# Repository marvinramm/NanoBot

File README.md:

# NanoBot

**Line-following robot for RoboCup Junior Rescue Line, where the PCB is the chassis. It has an ESP32, eight light sensors, two colour sensors, three ToF distance sensors, a gyro, a gripper arm, and its own firmware, NanoOS.**

I built the NanoBot in 2022–2023 as my RoboCup robot. The motors, wheels and sensors mount straight onto the PCB, so the robot needs no separate chassis and stays at 113 × 101 mm. I designed the electronics, the 3D-printed mechanics and the firmware myself, over two hardware revisions.

## The task

In Rescue Line, the robot follows a black line on its own through a course of tiles. Along the way it has to handle:

- gaps in the line
- intersections with green markers that set the direction
- speed bumps, ramps and obstacles

At the end, a silver strip marks the entrance to the evacuation zone.

## Features

- **PCB as chassis:** four DC motors in 3D-printed mounts, TPE tires that grip, and a TB6612FNG driver
- **Light sensor bar:**
  - phototransistors with white LEDs under a printed light shield
  - outer sensors on both sides
  - two TCS34725 colour sensors for the green markers
  - a reflection sensor for the silver strip
- **Three ToF distance sensors** (VL53L1X) for obstacles and walls
- **MPU6050 gyro** for ramps and exact turns
- **Two servo outputs**, e.g. for the gripper arm
- **0.96" OLED and rotary encoder** for:
  - a menu to start the run
  - calibration of light and colour values, stored in the EEPROM
  - sensor read-outs and a system check
- **Power:**
  - 2S Li-Po via XT30
  - USB-C charger with cell balancing
  - undervoltage protection and a battery switch
  - its own buck converter for constant motor speed
- **Over-the-air updates** over Wi-Fi, and a contest mode that starts the run right after power-on
- **Mount and 5 V / 4 A supply for an NVIDIA Jetson Nano** for image processing (REV1)

## How it works

```mermaid
flowchart LR
    PT["Phototransistors<br/>+ white LEDs"] --> MUX["CD74HC4067<br/>analog mux"] --> ESP["ESP32<br/>NanoOS"]
    TCA["TCA9548A I²C mux<br/>3 × VL53L1X · 2 × TCS34725"] <--> ESP
    BUS["I²C<br/>MPU6050 · OLED"] <--> ESP
    ENC["Rotary encoder"] --> ESP
    ESP --> SR["74HC595<br/>shift registers"]
    SR --> DRV["TB6612FNG"]
    ESP -- PWM --> DRV --> MOT["4 DC motors"]
    SR --> LED["Sensor LEDs<br/>RGB illumination"]
    ESP -- PWM --> SERVO["2 servos<br/>gripper arm"]
```

The ESP32 reads the phototransistors through the analog multiplexer. The colour and ToF sensors share one I²C address, so each one sits on its own channel of the TCA9548A. Shift registers save GPIOs: they set the motor directions and switch the sensor LEDs.

NanoOS keeps the line between the outer sensors with a proportional correction. It decides on every tile what to do (turn, green marker, gap, dead end, obstacle) and uses the gyro angle to switch to its own speeds on ramps and speed bumps.

## Revisions

| | REV1 (2022) | REV2 (2023) |
|---|---|---|
| **Status** | Stable, used with the Jetson Nano | Prototype with known issues (e.g. the reset button does not work) |
| **Light sensors** | 5 phototransistors, 2 × TCS34725 | 8 phototransistors incl. outer sensors and a reflection sensor, RGB illumination, 2 × TCS34725 |
| **Distance** | 3 × VL53L0X | 3 × VL53L1X |
| **Power** | LM2576 5 V / 4 A for the Jetson Nano, AMS1117 | adds USB-C charger, balancing, undervoltage protection, battery switch, motor buck converter |
| **Antenna** | 2 × U.FL | SMA |
| **Firmware** | [NanoOS 0.80](firmware/NanoOS-REV1) | [NanoOS 1.15](firmware/NanoOS) |

The lessons from both boards went into [**RoboCore**](https://github.com/marvinramm/RoboCore). RoboCore is a much smaller Raspberry Pi HAT that splits real-time control (ESP32-S3) and image processing (Pi).

## Repository layout

```
firmware/NanoOS/          NanoOS 1.15 for REV2 (Arduino sketch)
firmware/NanoOS-REV1/     NanoOS 0.80, the last version for REV1
hardware/nanobot-rev1/    Schematic, BOM, ESP32 pin assignment
hardware/nanobot-rev2/    Schematic, BOM, ESP32 pin assignment, EAGLE source
hardware/mechanical/      3D-printed parts: motor mounts, rims, tires, light shields, encoder knob
docs/images/              Pictures used in this README
```

Gerber files and ready-to-flash firmware images are attached to the [releases](https://github.com/marvinramm/NanoBot/releases). Libraries, Arduino settings and flashing are described in [`firmware/README.md`](firmware/README.md).

## License

© 2022–2023 Marvin Ramm. Open source with attribution:

- Code (`firmware/`): [MIT](LICENSE)
- Hardware and documentation: [CC BY 4.0](hardware/LICENSE)

Commercial use is allowed. Credit "NanoBot by Marvin Ramm" with a link to this repository. Details are in [LICENSING.md](LICENSING.md).

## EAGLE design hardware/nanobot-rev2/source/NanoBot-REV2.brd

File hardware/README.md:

# Hardware

| Folder | Content |
|---|---|
| [`nanobot-rev1`](nanobot-rev1) | REV1 (November 2022): schematic (PDF), BOM, ESP32 pin assignment |
| [`nanobot-rev2`](nanobot-rev2) | REV2 (April 2023): schematic (PDF), BOM with LCSC part numbers, ESP32 pin assignment, EAGLE 9.6 schematic and board in `source/` |
| [`mechanical`](mechanical) | 3D-printed parts (3MF / STL) |

The Gerber, drill and pick-and-place files of both revisions are attached to the [releases](https://github.com/marvinramm/NanoBot/releases).

**Build REV1.** REV2 works only partly (e.g. the reset button does not work) and is published as a reference for its power section: USB-C charger, cell balancing, undervoltage protection and battery switch.

The EAGLE source of REV2 uses parts from my own libraries; they are embedded in the `.sch` / `.brd` files, so the design opens without them.

## Pin assignment

The `*_ESP32_pinout.csv` files list every ESP32 GPIO with its function on the board. Sensors behind the analog multiplexer and the shift registers are mapped in `Pins.h` of the matching firmware ([REV2](../firmware/NanoOS/Pins.h), [REV1](../firmware/NanoOS-REV1/Pins.h)).

## License

The hardware design files, 3D models and documentation are licensed under [CC BY 4.0](LICENSE). See [LICENSING.md](../LICENSING.md) for the attribution text.

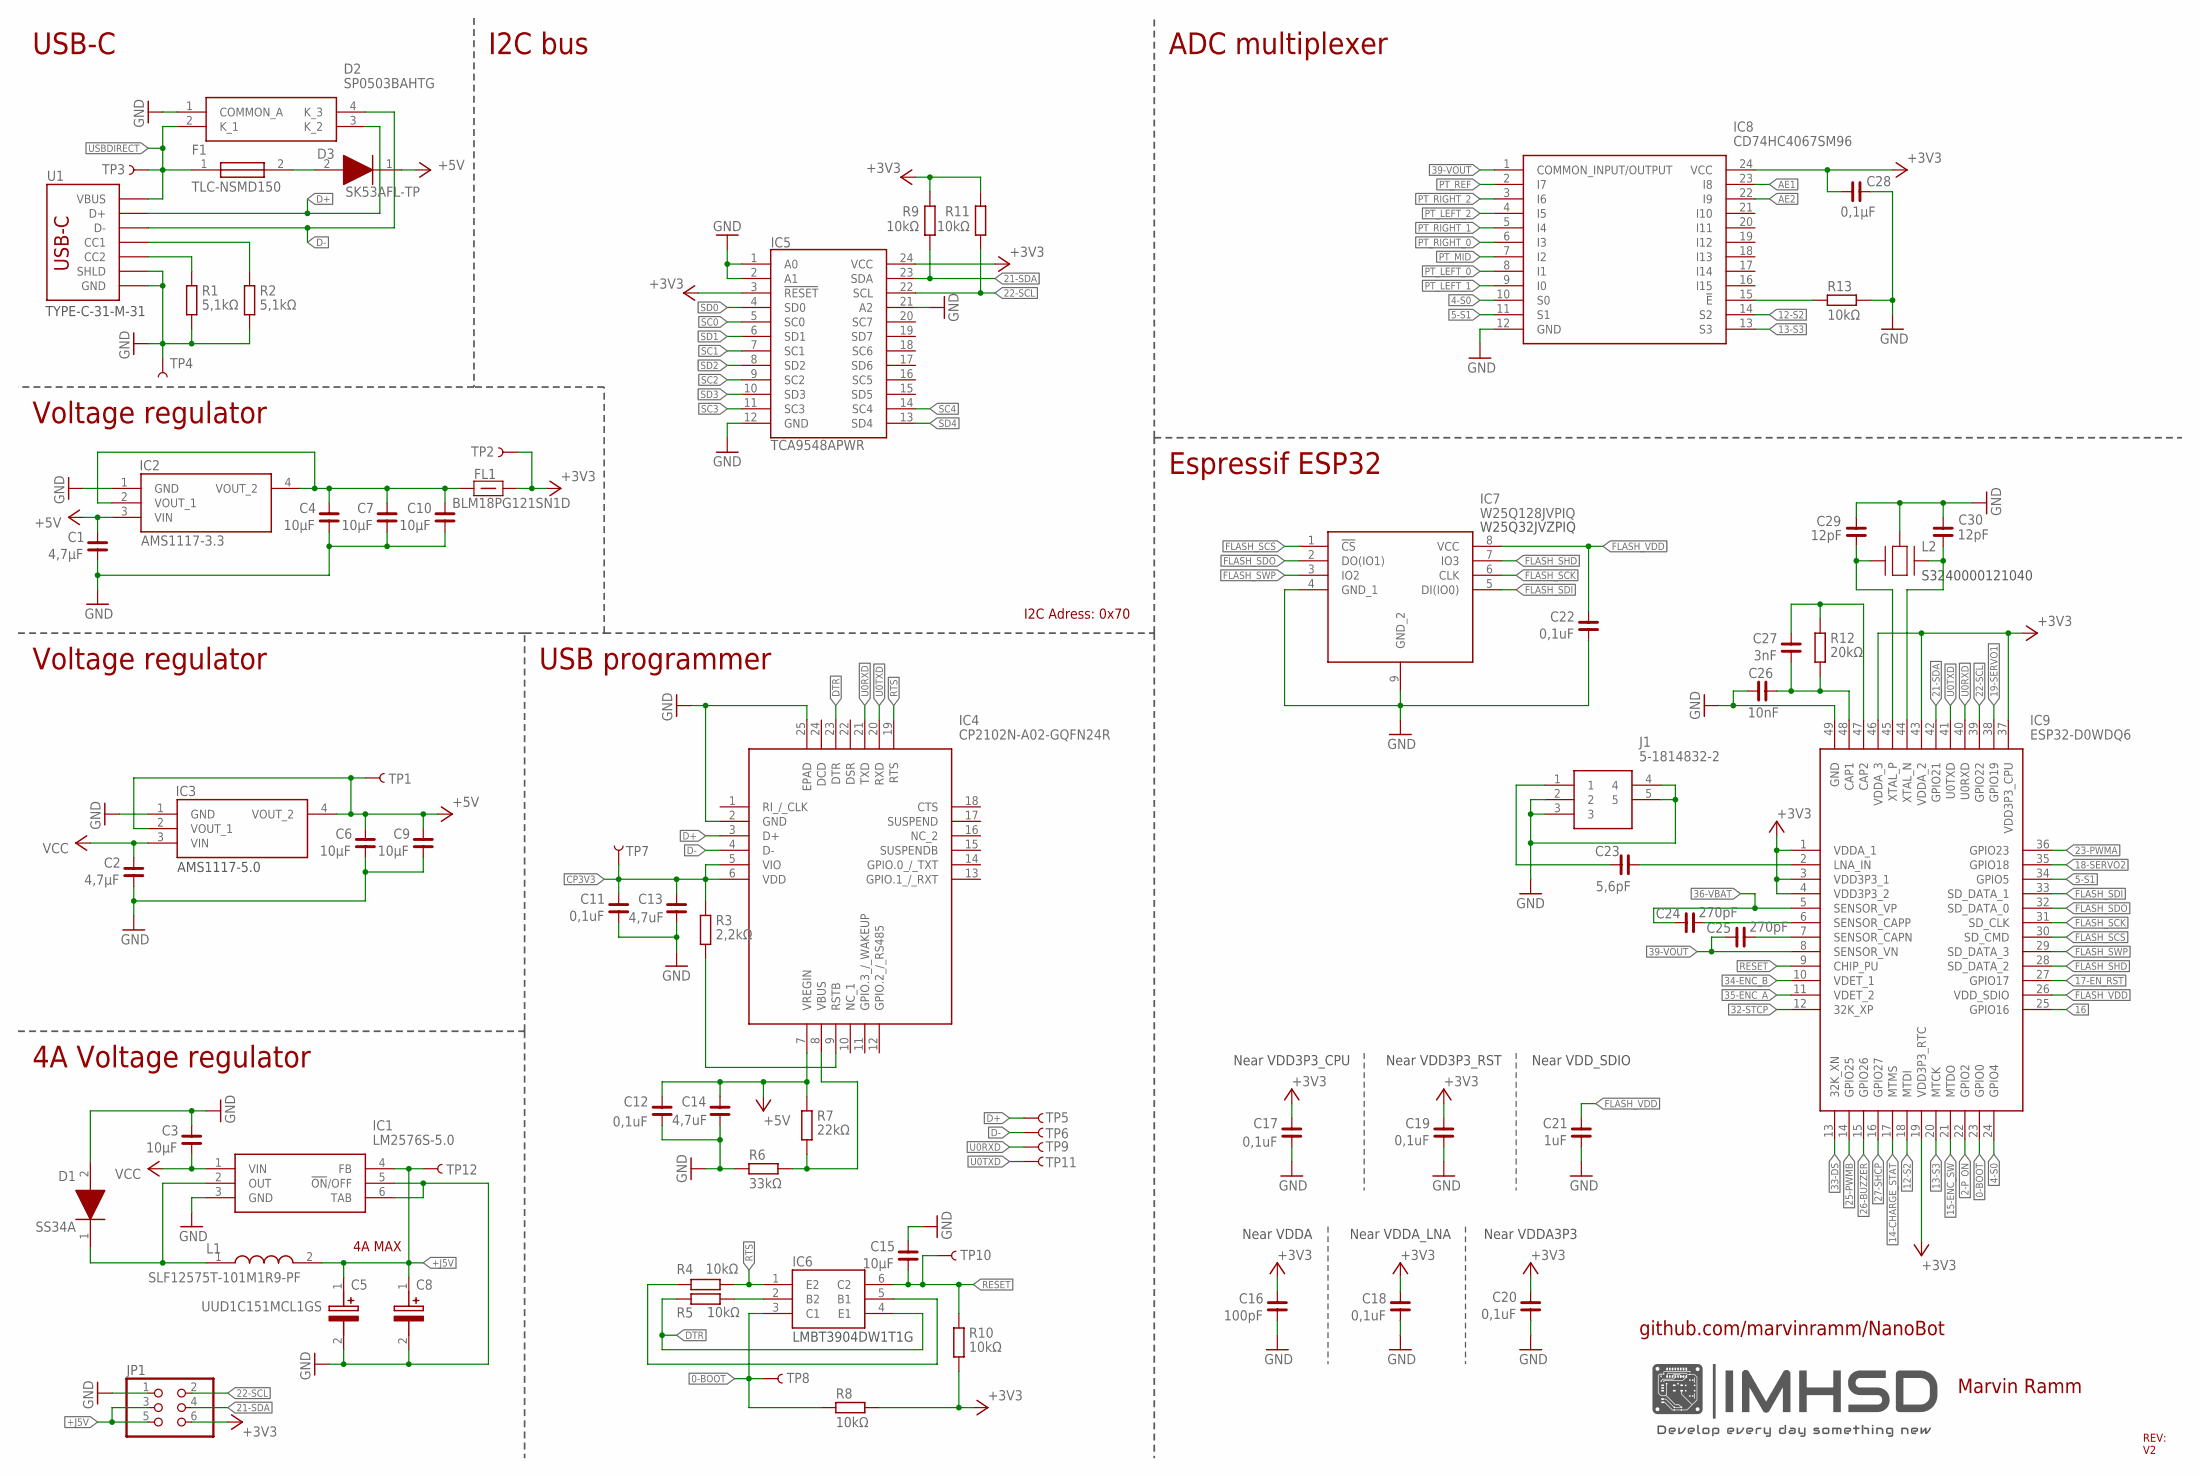
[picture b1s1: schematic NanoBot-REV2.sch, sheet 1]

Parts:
C1, C2: 4,7µF; C0603
C3, C4, C6, C7, C9, C10, C15: 10µF; C0603
C5, C8: UUD1C151MCL1GS; CAPAE660X800N
C11, C12, C17, C18, C19, C20, C22: 0,1uF; C0402
C13, C14: 4,7uF; C0402
C16: 100pF; C0402
C21: 1uF; C0402
C23: 5,6pF; C0402
C24, C25: 270pF; C0402
C26: 10nF; C0402
C27: 3nF; C0402
C28: 0,1µF; C0402
C29, C30: 12pF; C0402
D1: SS34A; DIOM5026X262N
D2: SP0503BAHTG
D3: SK53AFL-TP; SODFL5026X120N
F1: NANOSMDC020F-2; FUSC3216X82N
FL1: BLM18PG121SN1D; BLM18AG102BH1D
IC1: LM2576S-5.0; KTT0005B
IC2, IC3: AMS1117-3.3; SOT229P700X180-4N
IC4: CP2102N-A02-GQFN24R; QFN50P400X400X80-25N
IC5: TCA9548APWR; SOP65P640X120-24N
IC6: MMDT3904-TP; SOT65P230X120-6N
IC7: W25Q128JVPIQ; SON127P800X600X80-9N
IC8: CD74HC4067SM96; SOP65P780X200-24N
IC9: ESP32-D0WDQ6; QFN40P600X600X90-49N
J1: 5-1814832-2; 518148322
JP1: PINHD-2X3; 2X03
L1: SLF12575T-101M1R9-PF; SLF12575
L2: SMD-3225_4P16MHZ_20PF_10PPM_-4; SMD3225_4P16MHZ20PF10PPM4085
R1, R2: 5,1kΩ; R0402
R3: 2,2kΩ; R0402
R4, R5, R8, R9, R10, R11, R13: 10kΩ; R0402
R6: 33kΩ; R0402
R7: 22kΩ; R0402
R12: 20kΩ; R0402
TP1, TP2, TP3, TP4, TP5, TP6, TP7, TP8, TP9, TP10, TP11, TP12: TEST-POINT3X5; PAD.03X.05
U1: TYPE-C-31-M-14; TYPE-C-31-M-14_HRO

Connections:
0-BOOT: IC6.3 (C1), IC9.23 (GPIO0), R8.2, TP8.1
2-P_ON: IC9.22 (GPIO2); also elsewhere on the board
4-S0: IC8.10 (S0), IC9.24 (GPIO4)
5-S1: IC8.11 (S1), IC9.34 (GPIO5)
12-S2: IC8.14 (S2), IC9.18 (MTDI)
13-S3: IC8.13 (S3), IC9.20 (MTCK)
14-CHARGE_STAT: IC9.17 (MTMS); also elsewhere on the board
15-ENC_SW: IC9.21 (MTDO); also elsewhere on the board
16: IC9.25 (GPIO16); also elsewhere on the board
17-EN_RST: IC9.27 (GPIO17); also elsewhere on the board
18-SERVO2: IC9.35 (GPIO18); also elsewhere on the board
19-SERVO1: IC9.38 (GPIO19); also elsewhere on the board
21-SDA: IC5.23 (SDA), IC9.42 (GPIO21), JP1.4, R9.1; also elsewhere on the board
22-SCL: IC5.22 (SCL), IC9.39 (GPIO22), JP1.2, R11.1; also elsewhere on the board
23-PWMA: IC9.36 (GPIO23); also elsewhere on the board
25-PWMB: IC9.14 (GPIO25); also elsewhere on the board
26-BUZZER: IC9.15 (GPIO26); also elsewhere on the board
27-SHCP: IC9.16 (GPIO27); also elsewhere on the board
32-STCP: IC9.12 (32K_XP); also elsewhere on the board
33-DS: IC9.13 (32K_XN); also elsewhere on the board
34-ENC_B: IC9.10 (VDET_1); also elsewhere on the board
35-ENC_A: IC9.11 (VDET_2); also elsewhere on the board
36-VBAT: C24.1, IC9.5 (SENSOR_VP); also elsewhere on the board
39-VOUT: C25.1, IC8.1 (COMMON_INPUT/OUTPUT), IC9.8 (SENSOR_VN)
+3V3: C16.2, C17.2, C18.2, C19.2, C20.2, C28.1, FL1.1, IC5.3 (!RESET), IC5.24 (VCC), IC8.24 (VCC), IC9.1 (VDDA_1), IC9.3 (VDD3P3_1), IC9.4 (VDD3P3_2), IC9.19 (VDD3P3_RTC), IC9.37 (VDD3P3_CPU), IC9.43 (VDDA_2), IC9.46 (VDDA_3), JP1.6, R8.1, R9.2, R10.2, R11.2, TP2.1; also elsewhere on the board
+5V: C1.1, C6.1, C9.1, C12.2, C14.2, D3.1 (K), IC2.3 (VIN), IC3.2 (VOUT_1), IC3.4 (VOUT_2), IC4.7 (VREGIN), R7.1, TP1.1; also elsewhere on the board
+J5V: C5.1 (+), C8.1 (+), IC1.4 (FB), JP1.3, JP1.5, L1.2, TP12.1; also elsewhere on the board
AE1: IC8.23 (I8); also elsewhere on the board
AE2: IC8.22 (I9); also elsewhere on the board
CP3V3: C11.2, C13.2, IC4.5 (VIO), IC4.6 (VDD), R3.1, TP7.1
D+: D2.3 (K_2), IC4.3 (D+), TP5.1, U1.A6 (D+), U1.B6 (D+)
D-: D2.4 (K_3), IC4.4 (D-), TP6.1, U1.A7 (D-), U1.B7 (D-)
DTR: IC4.23 (DTR), IC6.4 (E1), R5.2
FLASH_SCK: IC7.6 (CLK), IC9.31 (SD_CLK)
FLASH_SCS: IC7.1 (!CS), IC9.30 (SD_CMD)
FLASH_SDI: IC7.5 (DI(IO0)), IC9.33 (SD_DATA_1)
FLASH_SDO: IC7.2 (DO(IO1)), IC9.32 (SD_DATA_0)
FLASH_SHD: IC7.7 (IO3), IC9.28 (SD_DATA_2)
FLASH_SWP: IC7.3 (IO2), IC9.29 (SD_DATA_3)
FLASH_VDD: C21.2, C22.2, IC7.8 (VCC), IC9.26 (VDD_SDIO)
GND: C1.2, C2.2, C3.1, C4.2, C5.2 (-), C6.2, C7.2, C8.2 (-), C9.2, C10.2, C11.1, C12.1, C13.1, C14.1, C15.1, C16.1, C17.1, C18.1, C19.1, C20.1, C21.1, C22.1, C26.1, C28.2, C29.1, C30.1, D1.2 (A), D2.1 (COMMON_A), IC1.3 (GND), IC1.5 (!ON!/OFF), IC1.6 (TAB), IC2.1 (GND), IC3.1 (GND), IC4.2 (GND), IC4.25 (EPAD), IC5.1 (A0), IC5.2 (A1), IC5.12 (GND), IC5.21 (A2), IC7.4 (GND_1), IC7.9 (GND_2), IC8.12 (GND), IC9.49 (GND), J1.2, J1.3, J1.4, J1.5, JP1.1, L2.2 (GND_2), L2.4 (GND_2), R1.2, R2.2, R6.2, R13.2, TP4.1, U1.A1B12 (GND), U1.B1A12 (GND), U1.P$1 (SHLD), U1.P$2 (SHLD), U1.P$3 (SHLD), U1.P$4 (SHLD), U1.P$5 (SHLD), U1.P$6 (SHLD), U1.P$7 (SHLD), U1.P$8 (SHLD), U1.P$9 (SHLD), U1.P$10 (SHLD), U1.P$11 (SHLD), U1.P$12 (SHLD), U1.P$14 (SHLD), U1.P$16 (SHLD), U1.P$18 (SHLD), U1.P$20 (SHLD); also elsewhere on the board
unnamed: C4.1, C7.1, C10.1, FL1.2, IC2.2 (VOUT_1), IC2.4 (VOUT_2)
unnamed: R1.1, U1.B5 (CC2)
unnamed: R2.1, U1.A5 (CC1)
unnamed: IC4.9 (RSTB), R3.2
unnamed: IC4.8 (VBUS), R6.1, R7.2
unnamed: IC8.15 (!E), R13.1
unnamed: C23.1, IC9.2 (LNA_IN)
unnamed: C26.2, C27.1, IC9.48 (CAP1), R12.2
unnamed: C27.2, IC9.47 (CAP2), R12.1
unnamed: C30.2, IC9.44 (XTAL_N), L2.3 (CRYSTAL_2)
unnamed: C29.2, IC9.45 (XTAL_P), L2.1 (CRYSTAL_1)
unnamed: C23.2, J1.1
unnamed: IC6.5 (B1), R4.2
unnamed: IC6.2 (B2), R5.1
unnamed: C25.2, IC9.7 (SENSOR_CAPN)
unnamed: D3.2 (A), F1.2
unnamed: C24.2, IC9.6 (SENSOR_CAPP)
unnamed: D1.1 (K), IC1.2 (OUT), L1.1
PT_LEFT_0: IC8.8 (I1); also elsewhere on the board
PT_LEFT_1: IC8.9 (I0); also elsewhere on the board
PT_LEFT_2: IC8.4 (I5); also elsewhere on the board
PT_MID: IC8.7 (I2); also elsewhere on the board
PT_REF: IC8.2 (I7); also elsewhere on the board
PT_RIGHT_0: IC8.6 (I3); also elsewhere on the board
PT_RIGHT_1: IC8.5 (I4); also elsewhere on the board
PT_RIGHT_2: IC8.3 (I6); also elsewhere on the board
RESET: C15.2, IC6.6 (C2), IC9.9 (CHIP_PU), R10.1, TP10.1; also elsewhere on the board
RTS: IC4.19 (RTS), IC6.1 (E2), R4.1
SC0: IC5.5 (SC0); also elsewhere on the board
SC1: IC5.7 (SC1); also elsewhere on the board
SC2: IC5.9 (SC2); also elsewhere on the board
SC3: IC5.11 (SC3); also elsewhere on the board
SC4: IC5.14 (SC4); also elsewhere on the board
SD0: IC5.4 (SD0); also elsewhere on the board
SD1: IC5.6 (SD1); also elsewhere on the board
SD2: IC5.8 (SD2); also elsewhere on the board
SD3: IC5.10 (SD3); also elsewhere on the board
SD4: IC5.13 (SD4); also elsewhere on the board
U0RXD: IC4.21 (TXD), IC9.40 (U0RXD), TP9.1
U0TXD: IC4.20 (RXD), IC9.41 (U0TXD), TP11.1
USBDIRECT: D2.2 (K_1), F1.1, TP3.1, U1.A4B9 (VBUS), U1.B4A9 (VBUS); also elsewhere on the board
VCC: C2.1, C3.2, IC1.1 (VIN), IC3.3 (VIN); also elsewhere on the board

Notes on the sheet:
AMS1117-5.0
S3240000121040
Near VDDA
Near VDDA_LNA
Near VDDA3P3
Near VDD3P3_CPU
Near VDD3P3_RST
Near VDD_SDIO
W25Q32JVZPIQ
TYPE-C-31-M-31
TLC-NSMD150
LMBT3904DW1T1G
4A MAX
Marvin Ramm
REV: V2
USB-C
I2C bus
ADC multiplexer
Espressif ESP32
Voltage regulator
4A Voltage regulator
USB programmer
I2C Adress: 0x70
github.com/marvinramm/NanoBot

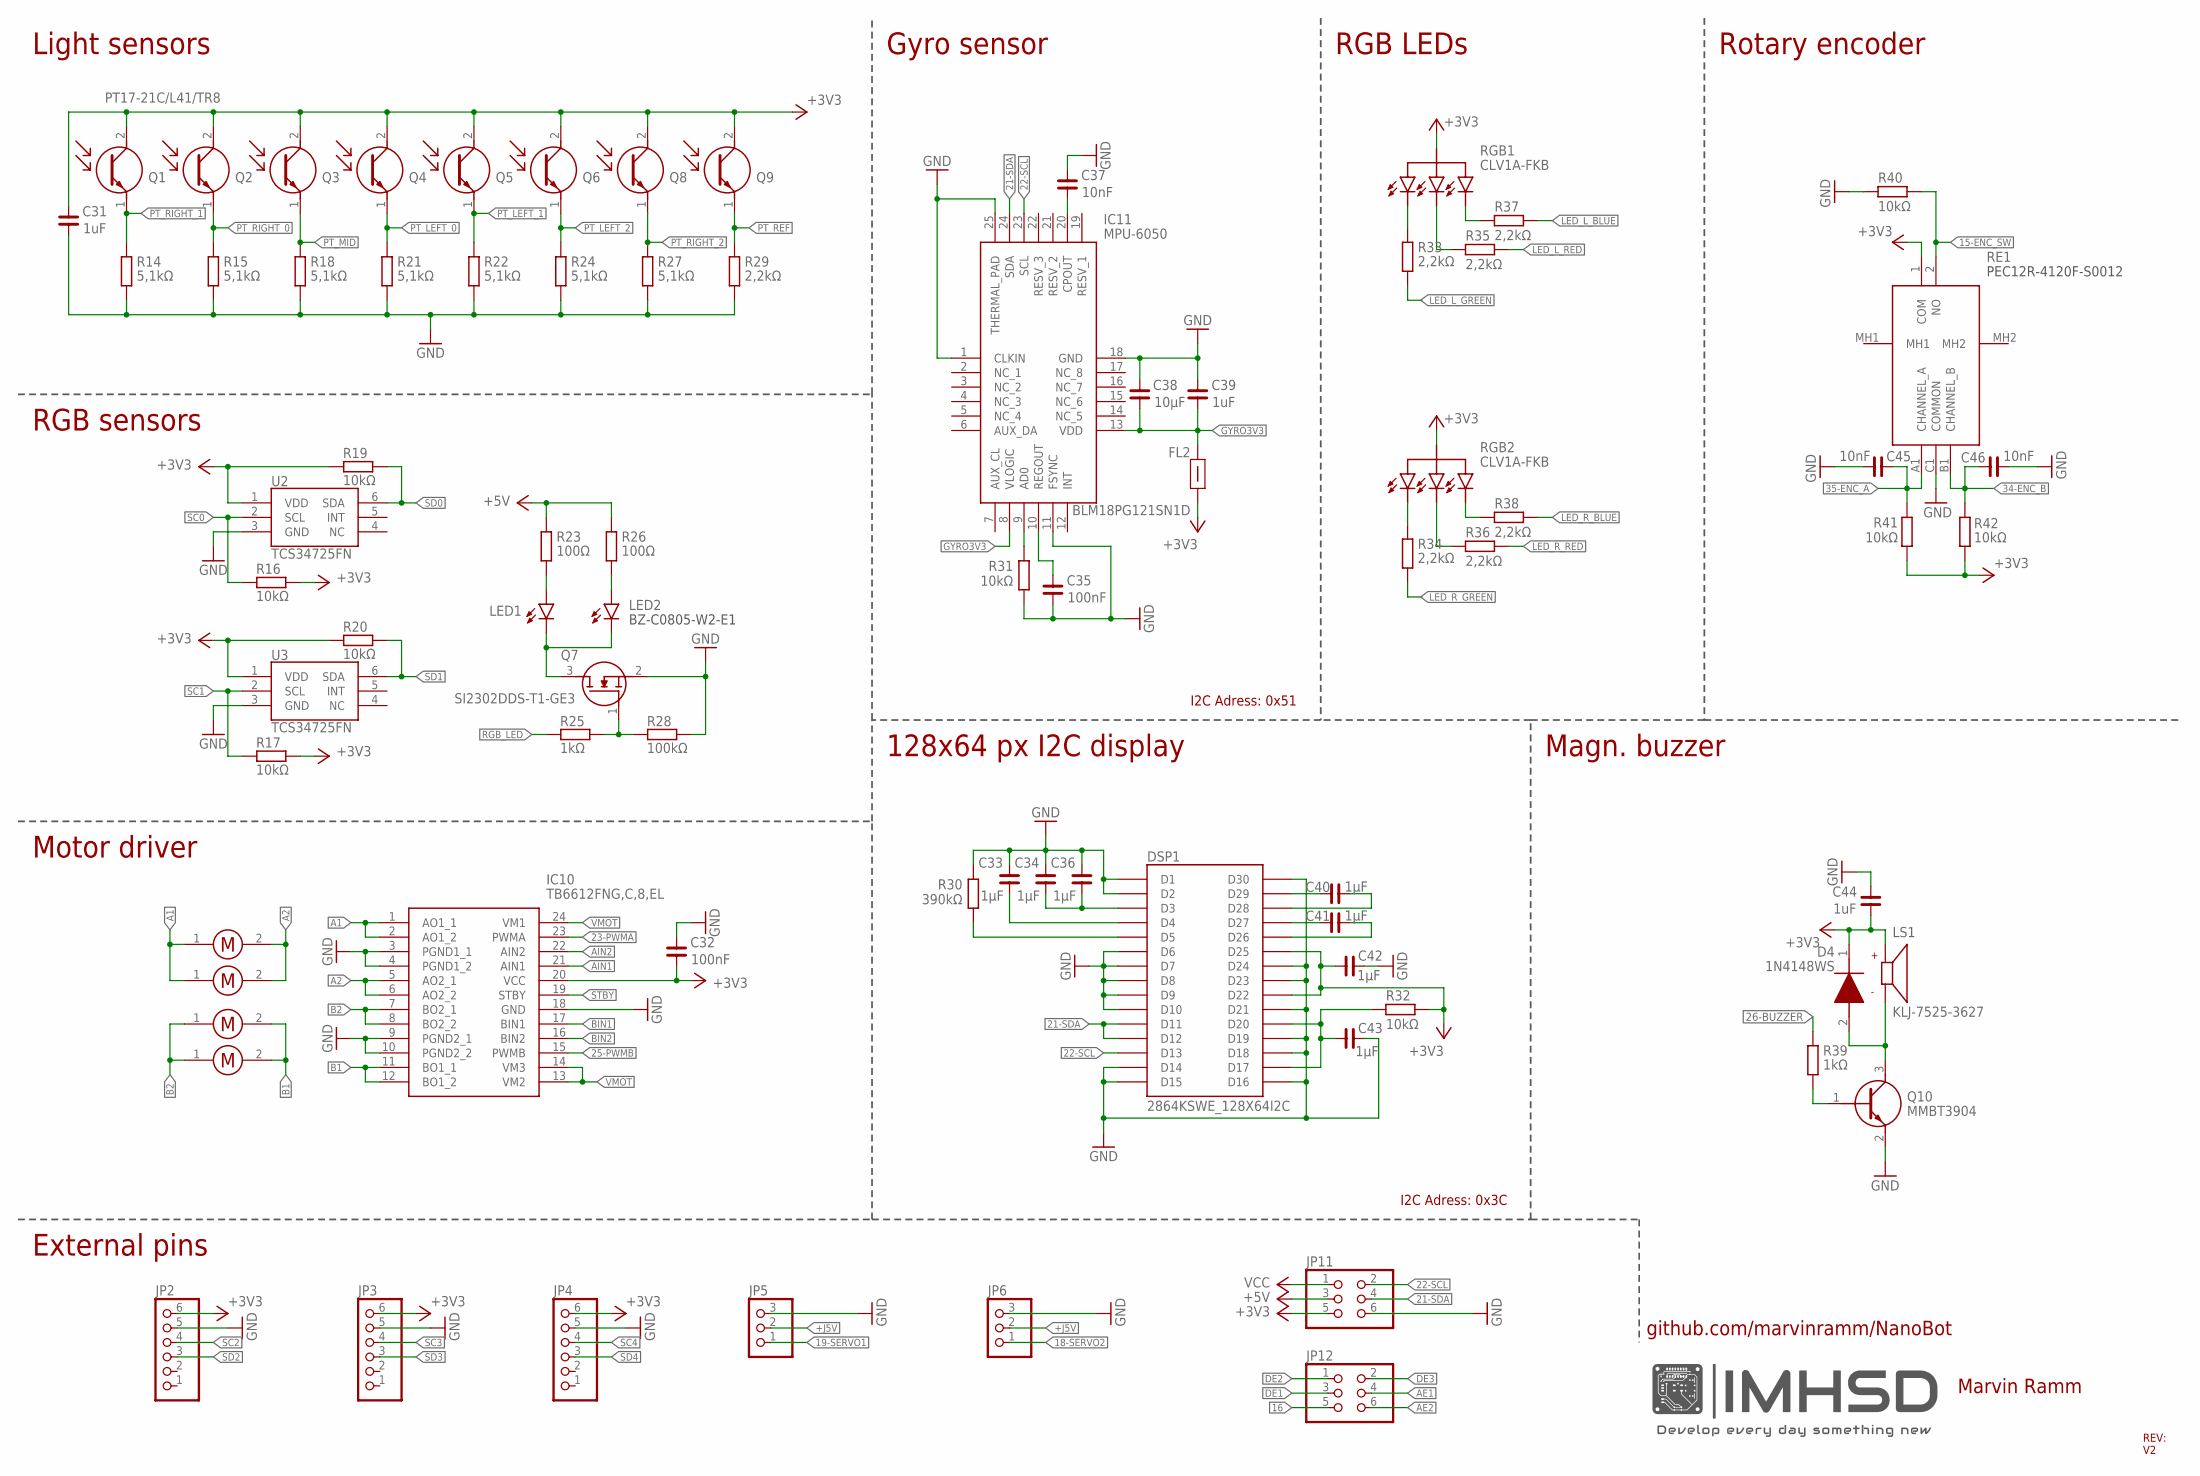
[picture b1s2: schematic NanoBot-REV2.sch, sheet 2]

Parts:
C31, C39, C44: 1uF; C0402
C32, C35: 100nF; C0402
C33, C34, C36, C40, C41, C42, C43: 1µF; C0402
C37, C45, C46: 10nF; C0402
C38: 10µF; C0603
D4: 1N4148WS; SODFL2512X90N
DSP1: 2864KSWE_128X64I2C
FL2: BLM18PG121SN1D; BLM18AG102BH1D
IC10: TB6612FNG,C,8,EL; SOP65P760X160-24N
IC11: MPU-6050; QFN50P400X400X95-25N
JP2, JP3, JP4: PINHD-1X6; 1X06
JP5, JP6: PINHD-1X3; 1X03
JP11, JP12: PINHD-2X3; 2X03
LED1, LED2: LEDCHIP-LED0805; CHIP-LED0805
LS1: CMT-7525-80-SMT-TR; XDCR_CMT-7525-80-SMT-TR
M1, M2, M3, M4: MOTOR_30RPM
Q1, Q2, Q3, Q4, Q5, Q6, Q8, Q9: PT17-21C/L41/TR8; 0805
Q7: SI2302DDS-T1-GE3; SOT95P237X112-3N
Q10: MMBT3904; SOT95P240X120-3N
R14, R15, R18, R21, R22, R24, R27: 5,1kΩ; R0402
R16, R17, R19, R20, R31, R32, R40, R41, R42: 10kΩ; R0402
R23, R26: 100Ω; R0402
R25, R39: 1kΩ; R0402
R28: 100kΩ; R0402
R29, R33, R34, R35, R36, R37, R38: 2,2kΩ; R0402
R30: 390kΩ; R0402
RE1: PEC12R-4230F-S0024; PEC12R4230FS0024
RGB1, RGB2: RGBLED
U2, U3: TCS34725FN; FN_1

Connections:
15-ENC_SW: R40.2, RE1.2 (NO); also elsewhere on the board
16: JP12.5; also elsewhere on the board
18-SERVO2: JP6.1; also elsewhere on the board
19-SERVO1: JP5.1; also elsewhere on the board
21-SDA: DSP1.D11, DSP1.D12, IC11.24 (SDA), JP11.4; also elsewhere on the board
22-SCL: DSP1.D13, IC11.23 (SCL), JP11.2; also elsewhere on the board
23-PWMA: IC10.23 (PWMA); also elsewhere on the board
25-PWMB: IC10.15 (PWMB); also elsewhere on the board
26-BUZZER: R39.1; also elsewhere on the board
34-ENC_B: C46.1, R42.2, RE1.B1 (CHANNEL_B); also elsewhere on the board
35-ENC_A: C45.1, R41.2, RE1.A1 (CHANNEL_A); also elsewhere on the board
+3V3: C31.2, C32.1, C42.1, C44.1, D4.1 (K), DSP1.D22, DSP1.D25, FL2.1, IC10.20 (VCC), JP2.6, JP3.6, JP4.6, JP11.5, LS1.P, Q1.2 (C), Q2.2 (C), Q3.2 (C), Q4.2 (C), Q5.2 (C), Q6.2 (C), Q8.2 (C), Q9.2 (C), R16.1, R17.1, R19.2, R20.2, R32.2, R41.1, R42.1, RE1.1 (COM), RGB1.+5V, RGB2.+5V, U2.1 (VDD), U3.1 (VDD); also elsewhere on the board
+5V: JP11.3, R23.1, R26.1; also elsewhere on the board
+J5V: JP5.2, JP6.2; also elsewhere on the board
A1: IC10.1 (AO1_1), IC10.2 (AO1_2), M1.1, M2.1
A2: IC10.5 (AO2_1), IC10.6 (AO2_2), M1.2, M2.2
AE1: JP12.4; also elsewhere on the board
AE2: JP12.6; also elsewhere on the board
AIN1: IC10.21 (AIN1); also elsewhere on the board
AIN2: IC10.22 (AIN2); also elsewhere on the board
B1: IC10.11 (BO1_1), IC10.12 (BO1_2), M3.2, M4.2
B2: IC10.7 (BO2_1), IC10.8 (BO2_2), M3.1, M4.1
BIN1: IC10.17 (BIN1); also elsewhere on the board
BIN2: IC10.16 (BIN2); also elsewhere on the board
DE1: JP12.3; also elsewhere on the board
DE2: JP12.1; also elsewhere on the board
DE3: JP12.2; also elsewhere on the board
GND: C31.1, C32.2, C33.1, C34.1, C35.1, C36.1, C37.2, C38.1, C39.2, C42.2, C43.2, C44.2, C45.2, C46.2, DSP1.D1, DSP1.D2, DSP1.D6, DSP1.D7, DSP1.D8, DSP1.D9, DSP1.D10, DSP1.D14, DSP1.D15, DSP1.D16, DSP1.D18, DSP1.D19, DSP1.D21, DSP1.D23, DSP1.D24, DSP1.D30, IC10.3 (PGND1_1), IC10.4 (PGND1_2), IC10.9 (PGND2_1), IC10.10 (PGND2_2), IC10.18 (GND), IC11.1 (CLKIN), IC11.11 (FSYNC), IC11.18 (GND), IC11.25 (THERMAL_PAD), JP2.5, JP3.5, JP4.5, JP5.3, JP6.3, JP11.6, Q7.2 (S), Q10.2 (E), R14.2, R15.2, R18.2, R21.2, R22.2, R24.2, R27.2, R28.2, R29.2, R30.2, R31.1, R40.1, RE1.C1 (COMMON), U2.3 (GND), U3.3 (GND); also elsewhere on the board
GYRO3V3: C38.2, C39.1, FL2.2, IC11.8 (VLOGIC), IC11.13 (VDD)
LED_L_BLUE: R37.2; also elsewhere on the board
LED_L_GREEN: R33.2; also elsewhere on the board
LED_L_RED: R35.2; also elsewhere on the board
LED_R_BLUE: R38.2; also elsewhere on the board
LED_R_GREEN: R34.2; also elsewhere on the board
LED_R_RED: R36.2; also elsewhere on the board
unnamed: C37.1, IC11.20 (CPOUT)
unnamed: C35.2, IC11.10 (REGOUT)
unnamed: IC11.9 (AD0), R31.2
unnamed: LED1.A, R23.2
unnamed: LED2.A, R26.2
unnamed: LED1.C, LED2.C, Q7.3 (D)
unnamed: Q7.1 (G), R25.2, R28.1
unnamed: C41.1, DSP1.D27
unnamed: C43.1, DSP1.D17, DSP1.D20, R32.1
unnamed: C33.2, DSP1.D4
unnamed: C41.2, DSP1.D26
unnamed: C34.2, C36.2, DSP1.D3
unnamed: DSP1.D5, R30.1
unnamed: C40.1, DSP1.D29
unnamed: C40.2, DSP1.D28
unnamed: R33.1, RGB1.P3
unnamed: R37.1, RGB1.P1
unnamed: R35.1, RGB1.P2
unnamed: R34.1, RGB2.P3
unnamed: R38.1, RGB2.P1
unnamed: R36.1, RGB2.P2
unnamed: D4.2 (A), LS1.N, Q10.3 (C)
unnamed: Q10.1 (B), R39.2
PT_LEFT_0: Q4.1 (E), R21.1; also elsewhere on the board
PT_LEFT_1: Q5.1 (E), R22.1; also elsewhere on the board
PT_LEFT_2: Q6.1 (E), R24.1; also elsewhere on the board
PT_MID: Q3.1 (E), R18.1; also elsewhere on the board
PT_REF: Q9.1 (E), R29.1; also elsewhere on the board
PT_RIGHT_0: Q2.1 (E), R15.1; also elsewhere on the board
PT_RIGHT_1: Q1.1 (E), R14.1; also elsewhere on the board
PT_RIGHT_2: Q8.1 (E), R27.1; also elsewhere on the board
RGB_LED: R25.1; also elsewhere on the board
SC0: R16.2, U2.2 (SCL); also elsewhere on the board
SC1: R17.2, U3.2 (SCL); also elsewhere on the board
SC2: JP2.4; also elsewhere on the board
SC3: JP3.4; also elsewhere on the board
SC4: JP4.4; also elsewhere on the board
SD0: R19.1, U2.6 (SDA); also elsewhere on the board
SD1: R20.1, U3.6 (SDA); also elsewhere on the board
SD2: JP2.3; also elsewhere on the board
SD3: JP3.3; also elsewhere on the board
SD4: JP4.3; also elsewhere on the board
STBY: IC10.19 (STBY); also elsewhere on the board
VCC: JP11.1; also elsewhere on the board
VMOT: IC10.13 (VM2), IC10.14 (VM3), IC10.24 (VM1); also elsewhere on the board

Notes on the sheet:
KLJ-7525-3627
RGB1
CLV1A-FKB
Marvin Ramm
REV: V2
RGB sensors
Light sensors
Gyro sensor
Rotary encoder
Motor driver
External pins
128x64 px I2C display
Magn. buzzer
I2C Adress: 0x51
PEC12R-4120F-S0012
RGB2
BZ-C0805-W2-E1
RGB LEDs
github.com/marvinramm/NanoBot
JP12
I2C Adress: 0x3C

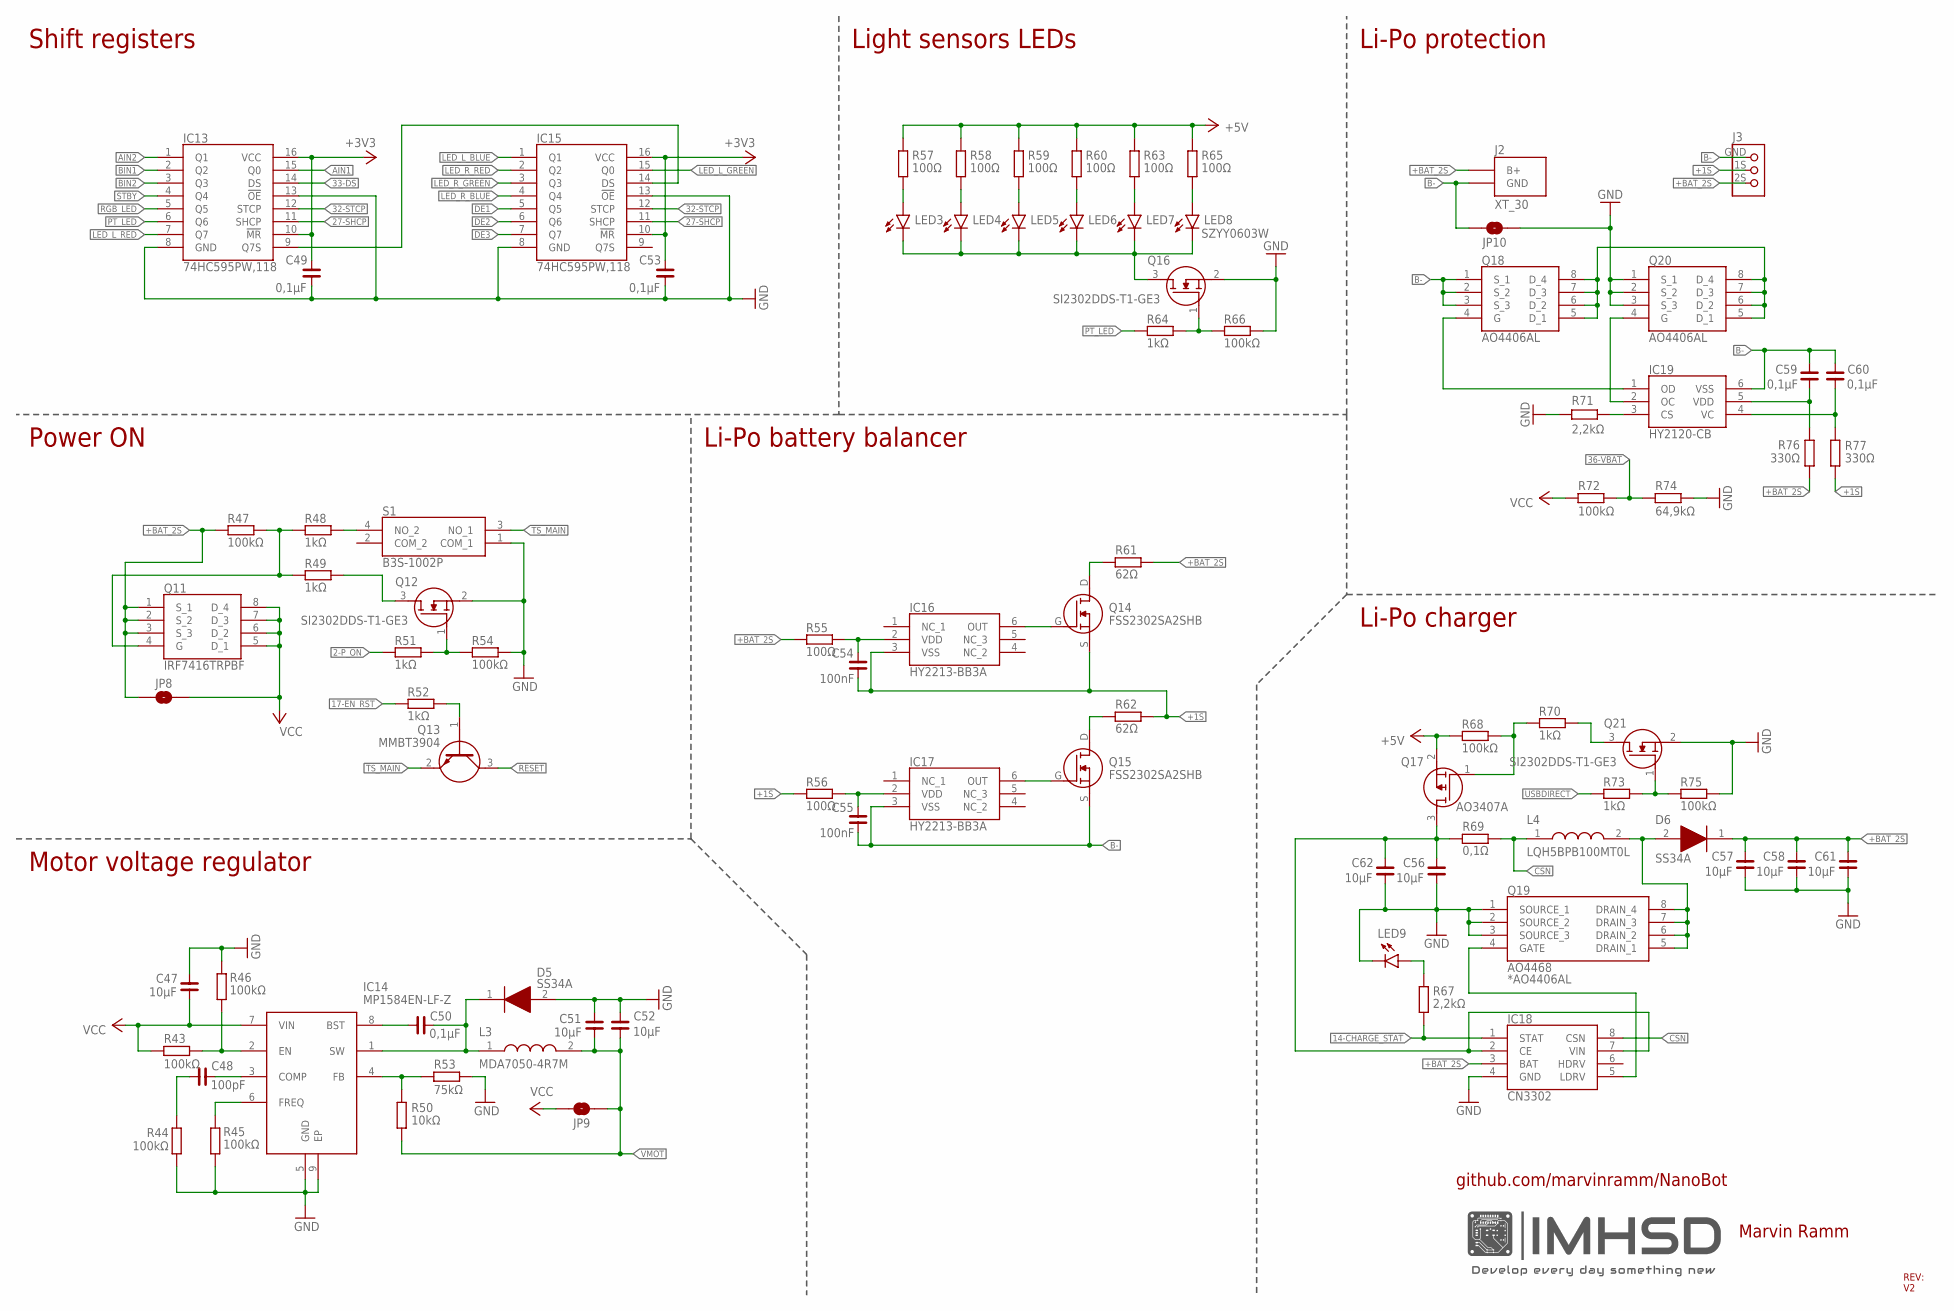
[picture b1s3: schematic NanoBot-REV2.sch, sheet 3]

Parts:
C47, C51, C52, C56, C57, C58, C61, C62: 10µF; C0603
C48: 100pF; C0402
C49, C50, C53, C59, C60: 0,1µF; C0402
C54, C55: 100nF; C0402
D5, D6: SS34A; DIOM5026X262N
IC13, IC15: 74HC595PW,118; SOP65P640X110-16N
IC14: MP1584EN-LF-Z; SOIC127P600X170-9N
IC16, IC17: HY2213-BB3A; SOT95P280X140-6N
IC18: CN3302
IC19: HY2120-CB; SOT95P280X140-6N
J2: XT_30
J3: 2SBALANCER
JP8, JP9, JP10: JUMPER-SMT_2_NO_SILK; SMT-JUMPER_2_NO_SILK
L3: MDA7050-4R7M
L4: LQH5BPB100MT0L
LED3, LED4, LED5, LED6, LED7, LED8, LED9: SZYY0603W; CHIP-LED0603
Q11: IRF7416TRPBF; SOIC127P600X175-8N
Q12, Q16, Q21: SI2302DDS-T1-GE3; SOT95P237X112-3N
Q13: MMBT3904; SOT95P240X120-3N
Q14, Q15: FSS2302SA2SHB
Q17: AO3407A; SOT95P280X125-3N
Q18, Q20: AO4406AL; SOIC127P600X175-8N
Q19: AO4468; SOIC127P600X175-8N
R43, R44, R45, R46, R47, R54, R66, R68, R72, R75: 100kΩ; R0402
R48, R49, R51, R52, R64, R70, R73: 1kΩ; R0402
R50: 10kΩ; R0402
R53: 75kΩ; R0402
R55, R56, R57, R58, R59, R60, R63, R65: 100Ω; R0402
R61, R62: 62Ω; R2512
R67, R71: 2,2kΩ; R0402
R69: 0,1Ω; R2512
R74: 64,9kΩ; R0402
R76, R77: 330Ω; R0402
S1: B3S-1002P; B3S1002P

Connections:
2-P_ON: R51.1; also elsewhere on the board
14-CHARGE_STAT: IC18.1 (STAT), R67.2; also elsewhere on the board
17-EN_RST: R52.1; also elsewhere on the board
27-SHCP: IC13.11 (SHCP), IC15.11 (SHCP); also elsewhere on the board
32-STCP: IC13.12 (STCP), IC15.12 (STCP); also elsewhere on the board
33-DS: IC13.14 (DS); also elsewhere on the board
36-VBAT: R72.2, R74.1; also elsewhere on the board
+1S: C54.2, IC16.3 (VSS), J3.1S (2), Q14.S, R56.1, R62.2, R77.2
+3V3: C49.1, C53.1, IC13.10 (!MR), IC13.16 (VCC), IC15.10 (!MR), IC15.16 (VCC); also elsewhere on the board
+5V: Q17.2 (S), R57.1, R58.1, R59.1, R60.1, R63.1, R65.1, R68.1; also elsewhere on the board
+BAT_2S: C57.1, C58.1, C61.1, D6.1 (K), IC18.3 (BAT), J2.B+, J3.2S (3), JP8.1, Q11.1 (S_1), Q11.2 (S_2), Q11.3 (S_3), R47.1, R55.1, R61.2, R76.1
AIN1: IC13.15 (Q0); also elsewhere on the board
AIN2: IC13.1 (Q1); also elsewhere on the board
B-: C55.2, C59.2, C60.2, IC17.3 (VSS), IC19.6 (VSS), J2.GND, J3.GND (1), JP10.2, Q15.S, Q18.1 (S_1), Q18.2 (S_2), Q18.3 (S_3)
BIN1: IC13.2 (Q2); also elsewhere on the board
BIN2: IC13.3 (Q3); also elsewhere on the board
CSN: IC18.8 (CSN), L4.1, R69.2
DE1: IC15.5 (Q5); also elsewhere on the board
DE2: IC15.6 (Q6); also elsewhere on the board
DE3: IC15.7 (Q7); also elsewhere on the board
GND: C47.1, C49.2, C51.1, C52.1, C53.2, C56.2, C57.2, C58.2, C61.2, C62.2, D5.2 (A), IC13.8 (GND), IC13.13 (!OE), IC14.5 (GND), IC14.9 (EP), IC15.8 (GND), IC15.13 (!OE), IC18.4 (GND), JP10.1, LED9.C, Q12.2 (S), Q16.2 (S), Q19.1 (SOURCE_1), Q19.2 (SOURCE_2), Q19.3 (SOURCE_3), Q20.1 (S_1), Q20.2 (S_2), Q20.3 (S_3), Q21.2 (S), R44.2, R45.2, R46.1, R53.1, R54.2, R66.2, R71.2, R74.2, R75.2, S1.1 (COM_1); also elsewhere on the board
LED_L_BLUE: IC15.1 (Q1); also elsewhere on the board
LED_L_GREEN: IC15.15 (Q0); also elsewhere on the board
LED_L_RED: IC13.7 (Q7); also elsewhere on the board
LED_R_BLUE: IC15.4 (Q4); also elsewhere on the board
LED_R_GREEN: IC15.3 (Q3); also elsewhere on the board
LED_R_RED: IC15.2 (Q2); also elsewhere on the board
unnamed: LED7.A, R63.2
unnamed: LED8.A, R65.2
unnamed: LED3.C, LED4.C, LED5.C, LED6.C, LED7.C, LED8.C, Q16.3 (D)
unnamed: Q16.1 (G), R64.2, R66.1
unnamed: LED6.A, R60.2
unnamed: IC14.2 (EN), R43.1, R46.2
unnamed: IC14.6 (FREQ), R45.1
unnamed: C48.2, IC14.3 (COMP)
unnamed: C48.1, R44.1
unnamed: C50.2, D5.1 (K), IC14.1 (SW), L3.1
unnamed: C50.1, IC14.8 (BST)
unnamed: IC13.9 (Q7S), IC15.14 (DS)
unnamed: LED5.A, R59.2
unnamed: LED4.A, R58.2
unnamed: LED3.A, R57.2
unnamed: R48.2, S1.4 (NO_2)
unnamed: Q11.4 (G), R47.2, R48.1, R49.1
unnamed: Q18.5 (D_1), Q18.6 (D_2), Q18.7 (D_3), Q18.8 (D_4), Q20.5 (D_1), Q20.6 (D_2), Q20.7 (D_3), Q20.8 (D_4)
unnamed: Q12.3 (D), R49.2
unnamed: Q12.1 (G), R51.2, R54.1
unnamed: IC19.1 (OD), Q18.4 (G)
unnamed: IC19.2 (OC), Q20.4 (G)
unnamed: IC19.3 (CS), R71.1
unnamed: C59.1, IC19.5 (VDD), R76.2
unnamed: C60.1, IC19.4 (VC), R77.1
unnamed: Q15.D, R62.1
unnamed: IC17.6 (OUT), Q15.G
unnamed: C55.1, IC17.2 (VDD), R56.2
unnamed: Q14.D, R61.1
unnamed: IC16.6 (OUT), Q14.G
unnamed: C54.1, IC16.2 (VDD), R55.2
unnamed: C56.1, C62.1, IC18.2 (CE), IC18.7 (VIN), Q17.3 (D), R69.1
unnamed: LED9.A, R67.1
unnamed: D6.2 (A), L4.2, Q19.5 (DRAIN_1), Q19.6 (DRAIN_2), Q19.7 (DRAIN_3), Q19.8 (DRAIN_4)
unnamed: Q17.1 (G), R68.2, R70.1
unnamed: IC18.5 (LDRV), Q19.4 (GATE)
unnamed: Q13.1 (B), R52.2
unnamed: Q21.3 (D), R70.2
unnamed: Q21.1 (G), R73.2, R75.1
unnamed: IC14.4 (FB), R50.1, R53.2
PT_LED: IC13.6 (Q6), R64.1
RESET: Q13.3 (C); also elsewhere on the board
RGB_LED: IC13.5 (Q5); also elsewhere on the board
STBY: IC13.4 (Q4); also elsewhere on the board
TS_MAIN: Q13.2 (E), S1.3 (NO_1)
USBDIRECT: R73.1; also elsewhere on the board
VCC: C47.2, IC14.7 (VIN), JP8.2, JP9.2, Q11.5 (D_1), Q11.6 (D_2), Q11.7 (D_3), Q11.8 (D_4), R43.2, R72.1; also elsewhere on the board
VMOT: C51.2, C52.2, JP9.1, L3.2, R50.2; also elsewhere on the board

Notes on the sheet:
Marvin Ramm
REV: V2
*AO4406AL
Shift registers
Power ON
Motor voltage regulator
Li-Po battery balancer
Light sensors LEDs
Li-Po protection
Li-Po charger
github.com/marvinramm/NanoBot

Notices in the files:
README.md:
License: MIT
License: CC BY 4.0
parts and their libraries:
rc-master-smd: Copyright (C) 2007, Bob Starr
SparkFun-Jumpers: Licensing: Creative Commons ShareAlike 4.0 International - https://creativecommons.org/licenses/by-sa/4.0
COPYRIGHT: Copyright (C) 2018 Accelerated Designs. All rights reserved
